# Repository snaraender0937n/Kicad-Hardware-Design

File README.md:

# 🧩 KiCad Hardware Design Project

## 🔍 Overview
This repository contains an **open-source hardware design project created using KiCad**, including complete **schematic diagrams**, **PCB layout**, and **manufacturing-ready outputs**.  
It is intended for **learning, reference, and practical PCB prototyping**.

---

## 🛠️ Tools Used
- 🧰 **KiCad** (Version 7 or later)

---

## 🖼️ PCB Preview
### 🔷 3D View

### 🔷 Top Layer

### 🔷 Bottom Layer

---

## 🗂️ Repository Structure
HARDWARE/ → KiCad schematic and PCB design files
IMAGES/ → Schematic, PCB layout, and 3D render images
BOM/ → Bill of Materials
GERBER/ → Manufacturing-ready Gerber files
---

## 🚀 How to Open the Project
1. Install **KiCad (v7 or later)**  
2. Clone this repository  
3. Open `project.kicad_pro` using KiCad  

---

## 📦 Project Outputs
- ✅ Complete schematic design  
- ✅ PCB layout (top & bottom layers)  
- ✅ 3D PCB visualization  
- ✅ Bill of Materials (BOM)  
- ✅ Gerber files for PCB fabrication  

---

## 📄 License
📜 This project is licensed under the  
MIT LICENSE

---

## 👤 Author
**Naraender**  

---

## ⭐ Notes
If you find this repository useful, consider **starring ⭐ it** and using it as a reference for your own KiCad projects.

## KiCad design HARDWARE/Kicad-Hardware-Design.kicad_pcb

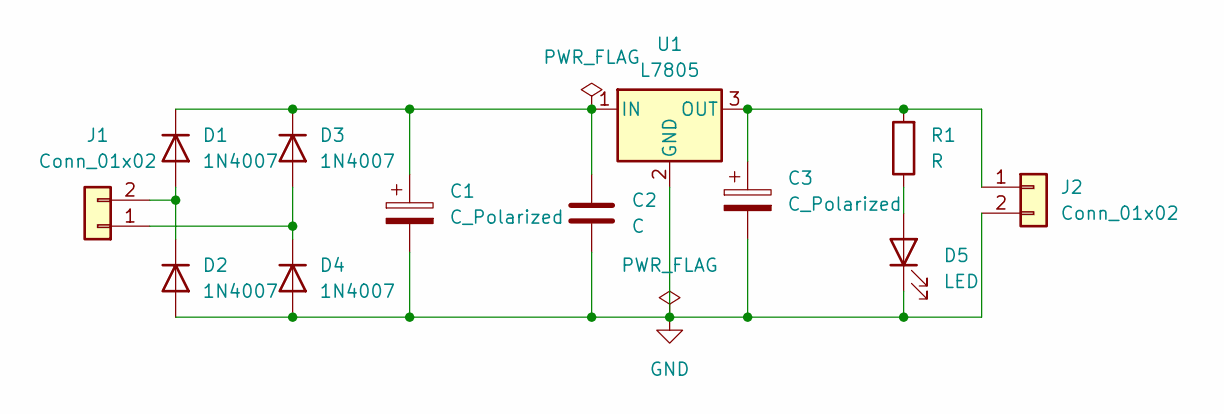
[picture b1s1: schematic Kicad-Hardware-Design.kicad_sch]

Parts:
C1: C_Polarized; CP_Radial_D12.5mm_P5.00mm
C2: C; C_Disc_D4.7mm_W2.5mm_P5.00mm
C3: C_Polarized; CP_Radial_D8.0mm_P5.00mm
D1, D2, D3, D4: 1N4007; D_DO-41_SOD81_P10.16mm_Horizontal
D5: LED; LED_D5.0mm_FlatTop
J1, J2: Conn_01x02; TerminalBlock_Phoenix_MKDS-1,5-2_1x02_P5.00mm_Horizontal
R1: R; R_Axial_DIN0411_L9.9mm_D3.6mm_P20.32mm_Horizontal
U1: L7805; TO-220-3_Vertical

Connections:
GND: C1.2, C2.2, C3.2, D2.2 (A), D4.2 (A), D5.1 (K), J2.2, U1.2 (GND)
unnamed: D1.2 (A), D2.1 (K), J1.2
unnamed: C1.1, C2.1, D1.1 (K), D3.1 (K), U1.1 (IN)
unnamed: D3.2 (A), D4.1 (K), J1.1
unnamed: D5.2 (A), R1.1
unnamed: C3.1, J2.1, R1.2, U1.3 (OUT)

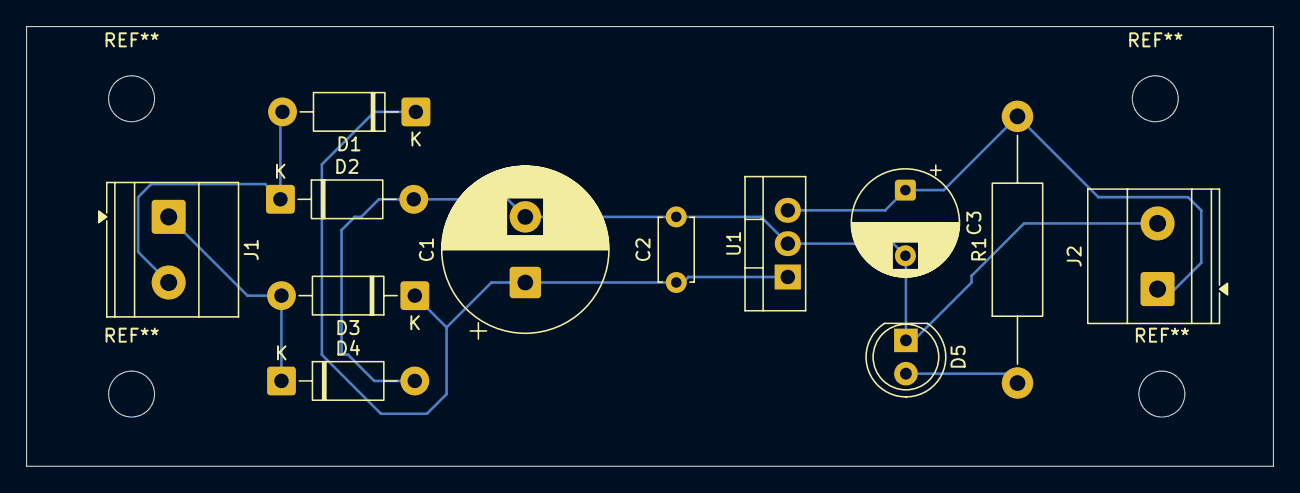
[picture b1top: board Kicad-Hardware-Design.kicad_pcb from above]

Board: 2 copper layers, 95.0 x 33.5 mm, 12 parts (0 on the bottom side), 6 nets.

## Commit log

2025-12-14 Revise README for improved structure and presentation
    Updated README.md with enhanced formatting and additional sections for clarity.
2025-12-14 Create del
2025-12-25 Update BOM CSV format and content
